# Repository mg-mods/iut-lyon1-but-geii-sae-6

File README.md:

# SAE 6 - Système d'alarme
Repo du projet **SAE 6 "système d'alarme"** réalisé dans le cadre de notre troisième année de BUT GEII à l'IUT Lyon 1.

## Concept initial
Notre projet consiste à développer un système d’alarme domestique complet, prêt à être installé sur une maison.

Les systèmes de surveillance actifs sont des détecteurs d’ouverture de portes et fenêtres ainsi qu’une caméra équipée de reconnaissance faciale à l’entrée.

L’interface utilisateur sera supportée par un M5Stack qui communiquera sans fil, en HF, avec le module central. À ce dernier sont reliés tous les différents composants (capteurs, reconnaissance faciale et alarme). L’interface permettra de verrouiller et déverrouiller le système d’alarme à l’aide d’un code à composer sur l’interface ou d’un badge RFID (à condition que la personne utilisant le badge soit reconnue par la reconnaissance faciale). Lorsqu’une intrusion est détectée, un module d’alarme est déclenché. 

Le module d'alimentation permet, en cas de coupure de courant, d'utiliser l'énergie stockée dans une batterie et de recharger cette dernière une fois le courant rétabli. Ce module d'alimentation est aussi responsable du déclenchement du mode dégradé permettant d'utiliser les modules critiques uniquement afin de réduire la consommation d'énergie. 

La communication étant critique, le système bascule en liaison BLE en cas de problème de communication en HF pour assurer une communication en permanence.

## Cahier des charges
### Cahier des charges initial :
- Détection d'ouverture d'une porte ou fenêtre
- Digicode pour déverrouiller l'alarme
- Reconnaissance faciale
- Alarme sonore
- Communication entre le digicode et la centrale en HF
- Protocole d'appairage entre le digicode et la centrale
- Détection d'erreur ou de signal anormal (sur les liaisons filaires)

### Améliorations possibles :
- Utilisation de badges RFID plutôt qu'un code, mais voir comment rendre cette solution sécurisée
- Communications en BLE si HF non fonctionnel
- Ajout d'une batterie et d'un mode dégradé en cas de coupure de courant
- Détecteur de mouvements
- Ajout d'un module GSM pour appeler le propriétaire et les forces de l'ordre ou un service de sécurité privée
- Ajout d'un bouton panique
- Empreinte biométrique

### Contraintes :
- Nécessité d'utiliser des capteurs à l'état haut par défaut pour détecter les failles
- Différenciation entre un capteur actif et un capteur absent ou endommagé

## Synoptique global initial
Au démarrage du projet, nous avions imaginé un fonctionnement bien précis pour notre système. Nous avons listé toutes les fonctionnalités que nous souhaitions implémenter et les avons reliées ensemble logiquement. L'ensemble du système tel que nous l'avions imaginé, sa décomposition en sous-systèmes et les interactions de ces derniers sont décrits ci-dessous :
[![](https://mermaid.ink/img/pako:eNqVVl1vokAU_SuTeWqz4opKUVKbtmhb0_oR6ma7G15GGJUUGDKMq67xv-8MCgysJa2JD3DuuWfu5dwLe-gQF0MDLnyycVaIMvBi2aEdAv5DPqLB7R7EKxRhAzgedXxcAz6aY98ANrwTOBgRd-1jcDEdmpc2BIcj1wncCqZJggCFbsYdaRI1QF6Yc925rwi-xB7xgPNUiuKoQtbi8BxTugNTLydFG5pz5sRnEmNKNpiCMWYbQt-PFKk3Shy9S1zX-6NQ7Mj81wijd0zjXO1IpNuctsJb-Yxv4CJp7KUsx9uprCWO74VlqR_DQvcVtv1YZPb2XeicHkPxsSlzxKSasI92EvMeMYbprsigC8-tPJv1MOyfnliRGYn-fqx2bL9MzC3ydW7G_FqFCeUT3RS2LNlYCVw_WAaSWkSJE8teTs4XgxEK0RIHOGQ2zMoUdlYcFFT21kQBpkjuDt4yxSWEqjkvJMxZlZl9HgPU_MQpr_kZXjNVlJ8JYNvG_Pa61xuOHybgGzCfBuZzr3eTVFLqpohFIvbpgUfevwxEXGrcM7FOOTadpPQAfI7FnydV6nXlRjJJEZ-f8IRfhJwTlFnzCJdNJ2JVITOd_BxYqdbZKCFmTsb94Ww4Gd-9gIxR6gi3JOD1JTDg7TWf7qzHpMxyGaXhSVQc-SwcKgzzB3mlGqXNBHq9vLdivRW3Fodn1vDxcWBlUcUVJcSeB79eZ9bkefB60ikuJXDGH4UgsU64kDnpDzJM8tj18YiZOf4fN5BHlEfpBB27XxoXIPnmlKk0GGcj0jyZlbgD9wCFXoCYR0IDLFDMpJcNN2Al7FTCanVytTq5WpE8mccU5bPP6BpL2LwCc85hsAaX1HOhIW7UIN9SvG_8Eu4Fz4ZsxfedDcVGcZF4u9rhgXMiFP4mJEhplKyXK2gskB_zq3Xkco2-h5YUBdldikMXU5OsQwYNVe90m0kaaOzhFhqK1mzU23q7q2taR-u2dK0Gd9Bo6lf1TrvV0lpNXW132u1DDf5NhNW6pnU77YbeVFW1oXWv9BrErscIHR0_lpJvpsM_bDXspg?type=png)](https://mermaid.live/edit#pako:eNqVVl1vokAU_SuTeWqz4opKUVKbtmhb0_oR6ma7G15GGJUUGDKMq67xv-8MCgysJa2JD3DuuWfu5dwLe-gQF0MDLnyycVaIMvBi2aEdAv5DPqLB7R7EKxRhAzgedXxcAz6aY98ANrwTOBgRd-1jcDEdmpc2BIcj1wncCqZJggCFbsYdaRI1QF6Yc925rwi-xB7xgPNUiuKoQtbi8BxTugNTLydFG5pz5sRnEmNKNpiCMWYbQt-PFKk3Shy9S1zX-6NQ7Mj81wijd0zjXO1IpNuctsJb-Yxv4CJp7KUsx9uprCWO74VlqR_DQvcVtv1YZPb2XeicHkPxsSlzxKSasI92EvMeMYbprsigC8-tPJv1MOyfnliRGYn-fqx2bL9MzC3ydW7G_FqFCeUT3RS2LNlYCVw_WAaSWkSJE8teTs4XgxEK0RIHOGQ2zMoUdlYcFFT21kQBpkjuDt4yxSWEqjkvJMxZlZl9HgPU_MQpr_kZXjNVlJ8JYNvG_Pa61xuOHybgGzCfBuZzr3eTVFLqpohFIvbpgUfevwxEXGrcM7FOOTadpPQAfI7FnydV6nXlRjJJEZ-f8IRfhJwTlFnzCJdNJ2JVITOd_BxYqdbZKCFmTsb94Ww4Gd-9gIxR6gi3JOD1JTDg7TWf7qzHpMxyGaXhSVQc-SwcKgzzB3mlGqXNBHq9vLdivRW3Fodn1vDxcWBlUcUVJcSeB79eZ9bkefB60ikuJXDGH4UgsU64kDnpDzJM8tj18YiZOf4fN5BHlEfpBB27XxoXIPnmlKk0GGcj0jyZlbgD9wCFXoCYR0IDLFDMpJcNN2Al7FTCanVytTq5WpE8mccU5bPP6BpL2LwCc85hsAaX1HOhIW7UIN9SvG_8Eu4Fz4ZsxfedDcVGcZF4u9rhgXMiFP4mJEhplKyXK2gskB_zq3Xkco2-h5YUBdldikMXU5OsQwYNVe90m0kaaOzhFhqK1mzU23q7q2taR-u2dK0Gd9Bo6lf1TrvV0lpNXW132u1DDf5NhNW6pnU77YbeVFW1oXWv9BrErscIHR0_lpJvpsM_bDXspg)

## Synoptique global final
À la fin du projet, certaines fonctionnalités n'ont pas pu être réalisées, que ce soit pour des raisons budgétaires ou que ces parties étaient trop chronophages. L'ensemble du système final, sa décomposition en sous-systèmes et les interactions de ces derniers sont décrits ci-dessous :
[![](https://mermaid.ink/img/pako:eNqNlV1v2jAUhv-K5atOI4x8AG1Upk6BtohRUGBaN-XGSQxETezIMYMO8d9nB0iclNEicZG87-NzfM6xs4MBDTG04SKmm2CFGAffXY94BIgfihFL7nYgW6EU2yCIWBDjBoiRj2MbePCb1MGYhusYg6vp0PnkQbA_sEESXiAdmiSIhAU7bitogiJSsqEfa5JX6LEwnEcZytILYV0h-5ixVzCNSijdsJLxacwVYko3mIEnzDeUvRwQpTZalr4obBwRjeFA5WcpRi-YZSoqSqOtt8oOoz917MewUkmNb5kCrPBW8c6fv7jP4OpY0moLNLaIwosJuvfD_rGWao6yBx-JKltRa52WhHGyTHhJpowGmdq_PFwGxoigJU4w4R4sIssWagFKLmbtoAQzpCaMt1wLKWV6yRHKg1Wd7AsP0MuMT5zxEc54y5nvcGPKMJDG7LhHtcKAb1v-3W2vN3y6n4DPwHkcOKNe72tehFojpBdJ7-O9dJym4owrkK65O3x4GLjSmo_qKawYdvkXYbVmUytEKVUMOhKG6eTnwJUuuX5V9lW5TLdqClSTyLhyeECvV2SXH6Tq-QBiE6PBr9ncnYwGs-OWqycCnKlcxSSnX4RxJv1BoSnVvz1kUBTv7QyD0lGfz6N02HptBsGhtupKtWl712GedZwiFWUWfdwBRKIE8YgSGyxQxpV7TXTxovwOHfxfzqfxpIrh52yNFc2_oAXnNNiASxaF0JYvGlAcb7Fz8Qh3kvMgX4mLwoPySIVIXsUe2QsmReQ3pckJY3S9XEF7geJMPK3TUMToR2jJUGnBJMTMoWvCoa23u_ka0N7BLbStblPvmkbLaOtWx7q2rAZ8laZO02iZht5pt42uaZnX-wb8m0dtNbtWW78xdat1Ywm9YzYgDiNO2fjwWc2_rvt_SVRXbA?type=png)](https://mermaid.live/edit#pako:eNqNlV1v2jAUhv-K5atOI4x8AG1Upk6BtohRUGBaN-XGSQxETezIMYMO8d9nB0iclNEicZG87-NzfM6xs4MBDTG04SKmm2CFGAffXY94BIgfihFL7nYgW6EU2yCIWBDjBoiRj2MbePCb1MGYhusYg6vp0PnkQbA_sEESXiAdmiSIhAU7bitogiJSsqEfa5JX6LEwnEcZytILYV0h-5ixVzCNSijdsJLxacwVYko3mIEnzDeUvRwQpTZalr4obBwRjeFA5WcpRi-YZSoqSqOtt8oOoz917MewUkmNb5kCrPBW8c6fv7jP4OpY0moLNLaIwosJuvfD_rGWao6yBx-JKltRa52WhHGyTHhJpowGmdq_PFwGxoigJU4w4R4sIssWagFKLmbtoAQzpCaMt1wLKWV6yRHKg1Wd7AsP0MuMT5zxEc54y5nvcGPKMJDG7LhHtcKAb1v-3W2vN3y6n4DPwHkcOKNe72tehFojpBdJ7-O9dJym4owrkK65O3x4GLjSmo_qKawYdvkXYbVmUytEKVUMOhKG6eTnwJUuuX5V9lW5TLdqClSTyLhyeECvV2SXH6Tq-QBiE6PBr9ncnYwGs-OWqycCnKlcxSSnX4RxJv1BoSnVvz1kUBTv7QyD0lGfz6N02HptBsGhtupKtWl712GedZwiFWUWfdwBRKIE8YgSGyxQxpV7TXTxovwOHfxfzqfxpIrh52yNFc2_oAXnNNiASxaF0JYvGlAcb7Fz8Qh3kvMgX4mLwoPySIVIXsUe2QsmReQ3pckJY3S9XEF7geJMPK3TUMToR2jJUGnBJMTMoWvCoa23u_ka0N7BLbStblPvmkbLaOtWx7q2rAZ8laZO02iZht5pt42uaZnX-wb8m0dtNbtWW78xdat1Ywm9YzYgDiNO2fjwWc2_rvt_SVRXbA)

## Organisation du repo
Chaque composant sera réparti dans des branches différentes de ce repo. Voici la liste des branches présentes :
- **main** : branche d'accueil du repo, laissée vide pour l'instant
- **alarm** : branche du module d'alarme (réalisée par Lilian CHARRIERE)
- **cmd** : branche du module de commande (ou "digicode", bien que cette appellation soit assez réductrice ; réalisée par Corentin DEBAISIEUX)
- **hf** : branche des transmissions HF et de la modulation du signal (réalisée par Gaspard DENIZOU)
- **hub** : branche du module principal (ou "hub" ; réalisée par Bastien PORTIER)
- **rasp** : branche du module de reconnaissance faciale (réalisée par Lilian CHARRIERE)

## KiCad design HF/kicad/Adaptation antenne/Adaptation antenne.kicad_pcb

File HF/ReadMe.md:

# Modulation haute fréquence

## Diagramme de fonctionnement théorique

| | Valeur |
| ------ | ------ |
| Signal UART | 9600 bps |
| Fréquence porteuse | 100 kHz |
| Fréquence d'émission | 13,56 MHz |
| Puissance d'émission | 10 dBm |

```mermaid
---
config:
  theme: forest
  themeVariables:
    lineColor: '#FFA100'

---

stateDiagram
  direction TB
  state modulation {
    direction TB
    Mi1 --> V1
    Ol1 --> PB1
    V1 --> PB2
    PB2 --> Me1 :Tension=100mVpp P = 14DBm
    PB1 --> Me1 :Tension =1 a 2 Vpp P = 4-10DBm
    Me1 --> [*]
    Mi1
    V1
    Ol1
    PB1
    PB2
    Me1
  }
  state Démodulation {
    direction TB
    [*] --> G
    G-->PD
    PD --> Me2
    Ol2 --> Me2
    Me2 --> PB3
    PB3 --> PLL
    PLL --> PB4
    PB4 -->trig
     trig -->Mi2
[*]    Me2
    Ol2
    PB3
    PLL
    Mi2
  }
  modulation --> Démodulation
  Mi1:Microcontrôleur
  V1:VCO
  Ol1:Oscillateur local 13 MHz
  PB1:Filtre passe-bas fc=13,56 MHz
  PB2:Filtre passe-bas Fc=100 kHz ordre 2
  Me1:Mélangeur
  Me2:Mélangeur
  Ol2:Oscillateur local 13 MHz
  PB3:Filtre passe-bande centré sur 100 kHz ordre 2
  PB4:Filtre passe-bas Fc=20 kHz ordre 2
  trig:Trigger de Schmitt
  PD:Pont de diodes
  G:Gain 10 dBm
```

Le gain de la partie démodulation se fait avec un AOP transimpédance si, à la sortie de l'antenne, on doit amplifier le signal.  
Le pont diviseur sert à bien avoir la bonne puissance en entrée du mélangeur.

## Simulation LTspice

Le VCO, la PLL et les mélangeurs n'étant pas répertoriés sur LTspice, ils sont simulés avec des lignes de commande.

| Composant | Ligne de commande |
| ------ | ------ |
| VCO modulation | `Bvco vcomod 0 V = 2.5 + 2.5*sgn(sin(2*pi*idt( {Fp}*(1 + 0.05*(V(microout) - 0.5)) )))` |
| Mélangeur modulation | `bvmel1 mel 0 V = V(filtre_100k)*V(filtre_13M)` |
| VCO démodulation | `Bvcodemod Vco 0 V = 2.5 + 2.5*sgn(sin(2*pi*idt( {Fp}*(1 + 0.1*(V(Demodul) - 0.5)))))` |
| Mélangeur démodulation | `bvmel2 mel2 0 V = V(mel)*V(oscilateur)` |

### Paramètres de simulation

| Paramètre | Valeur |
| ------ | ------ |
| Tsim | 5 ms |
| F | 9600 Hz |
| F13 | 13 560 000 Hz |
| Fp | 100 000 Hz |

## Schémas KiCad théoriques

L'adaptation d'impédance de l'antenne se fait sur une petite carte reliée par un câble BNC.

## Mise en pratique

Lors de la livraison des composants, nous n'avons pas reçu de 74HC4046 mais des CD4046BE. Bien que ce composant ait les mêmes fonctionnalités que le composant que nous avions choisi, son dimensionnement est bien différent pour les valeurs de résistance nécessaires.

Le VCO n'oscille plus à 100 kHz mais autour de 130 kHz. C'est entre autres dû à la datasheet du composant, qui n'est pas très lisible :

[lien datasheet CD4046BE](https://www.ti.com/lit/ds/symlink/cd4046b.pdf?HQS=dis-dk-null-digikeymode-dsf-pf-null-wwe&ts=1780683578275&ref_url=https%253A%252F%252Fwww.ti.com%252Fgeneral%252Fdocs%252Fsuppproductinfo.tsp%253FdistId%253D10%2526gotoUrl%253Dhttps%253A%252F%252Fwww.ti.com%252Flit%252Fgpn%252Fcd4046b)

## Travail réalisé

- [x] VCO et modulation à basse fréquence
- [x] PLL et démodulation à basse fréquence
- [ ] Utilisation du mélangeur pour basculer en haute fréquence
- [ ] Adaptation en impédance de l'antenne
- [ ] Utilisation du mélangeur pour basculer en basse fréquence

## Test de bon fonctionnement

Pour vérifier le bon fonctionnement, j'ai effectué des mesures à l'oscilloscope en entrée et en sortie d'une liaison VCO-PLL avec, en entrée et en sortie, un microcontrôleur RP2040 choisi pour ses deux canaux UART et parce que les tensions de sortie UART correspondent aux microcontrôleurs utilisés dans notre système de surveillance (soit 3,3 V).

J'ai ensuite envoyé une série de 100 messages similaires à ceux qui sont envoyés entre le digicode et le hub, puis j'ai comparé le message d'origine avec le message reçu.

J'ai au maximum 10 messages reçus avec une erreur ou plus, soit 10 % d'erreur maximale de transmission en basse fréquence.

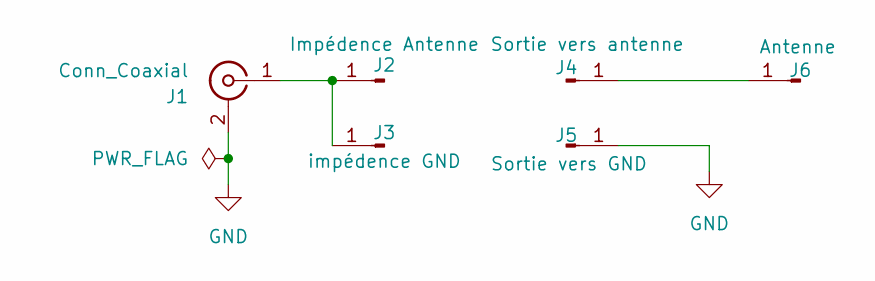
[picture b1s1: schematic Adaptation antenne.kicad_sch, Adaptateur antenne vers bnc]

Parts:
J1: Conn_Coaxial; Adaptateur BNC
J2: Impédence Antenne; PinHeader_1x01_P1.00mm_Vertical
J3: impédence GND; PinHeader_1x01_P1.00mm_Vertical
J4: Sortie vers antenne; PinHeader_1x01_P1.00mm_Vertical
J5: Sortie vers GND; PinHeader_1x01_P1.00mm_Vertical
J6: Antenne; PinHeader_1x01_P1.00mm_Vertical

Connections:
GND: J1.2 (Ext), J5.1
unnamed: J1.1 (In), J2.1, J3.1
unnamed: J4.1, J6.1

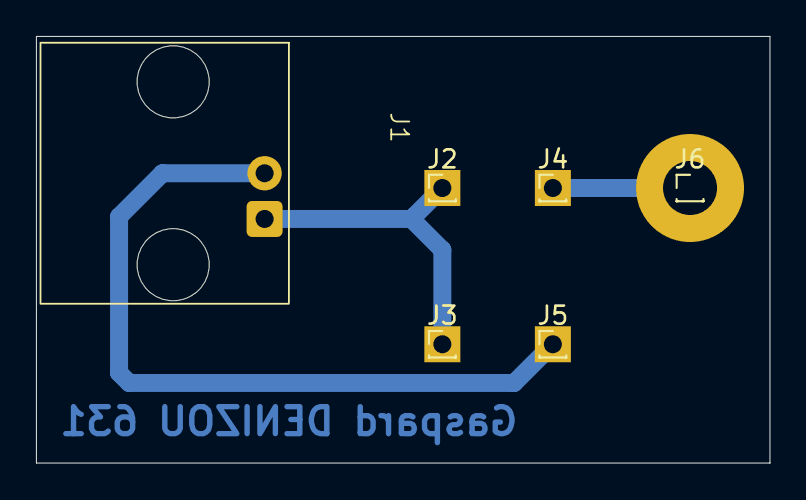
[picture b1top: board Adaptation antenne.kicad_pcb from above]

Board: 2 copper layers, 40.8 x 23.7 mm, 6 parts (0 on the bottom side), 3 nets.

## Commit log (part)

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2026-01-22 Premier essais
    Push and commit d'essais
2026-01-22 Add initial Hub project files and assets
    Added PlatformIO configuration, source, header, and documentation files for the Hub project targeting the M5Stack Core2 board. Included .gitignore, VSCode extension recommendations, image assets, and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
2026-01-22 ajout simulation du sommateur sur LTspice
2026-01-22 tentative PLL LTspice n°1
2026-01-23 Version bien de l'interface + sous-menu
    Removed houseLock.h and added images.h to manage image resources. Updated main.cpp to use the new images header. Replaced house-lock PNG with new SVG assets (exit, gear, restart, siren) and updated I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
2026-01-23 simu de la modulation et démodulation à 100k de porteuse
2026-01-27 Amélioration globale de l'interface
    Buttons are now managed via pointers with dynamic allocation and cleanup to improve memory handling. UI layout for options screen is updated for better consistency, and button initialization is separ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
2026-01-27 test rfid+image
2026-01-29 test readme avec schémas mermaid
2026-01-29 mermaid 2.0
2026-01-29 mermaid 3.0
2026-01-29 changement theme de mermaid
2026-01-29 changegement couleur ligne du schémas mermaid
2026-01-29 changement position filtre du schémas mermaid
2026-01-29 réparation des pb du schémas
2026-01-29 Connexion serie + affichage sur screen + ébauche RTC
    Introduces FreeRTOS queues and tasks for serial message reception and LCD display management. Adds message parsing, logging with timestamps, and dynamic display of messages on the home screen. Refact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
2026-01-30 Communication série interM5 fonctionnel
    Replace dynamic String with fixed char msg[TRAME_SIZE] in t_message_lcd to avoid heap allocations and copy incoming payloads with snprintf. Switch serial I/O to Serial2 (begin on pins 13/14 at 9600) 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
2026-01-30 Add files via upload
    test pour la liaison serie
2026-02-01 comit fin 2eme semaine
2026-02-07 modif graphique readme , ajout detail filtre et tension
2026-02-07 schemas bloque finit
2026-02-07 choix et dimmentionement presque terminer
2026-02-24 ajout fichier ltspice schémas total
2026-02-24 schémas de simulation de la liaison hf finit
2026-02-24 3-line scrolling display and serial parsing fix
    Introduce a 3-line scrolling buffer for the LCD and simplify serial message parsing. Incoming 'L...' frames no longer use a numeric line index; the code logs the full text, stores it in the message, 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
2026-02-24 Add files via upload
    ajout de task
2026-02-26 Passage du défilement à 4 lignes
    Increase the R1 region height from 80 to 85 for a slightly larger UI element. Remove an unused assignment to message.ligne. Expand the displayBuffer from 3 to 4 lines, adjust the scrolling copies and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
2026-02-26 Amélioration du défilement + post-factorisation
    Introduce a global displayBuffer[4][64] to hold the four LCD lines and initialize it in setup. drawHome now renders these buffered lines, and taskGestionLcd was updated to use the global buffer (loca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
2026-02-26 Factorisation du code
2026-02-27 Détection trame via Regex + check keyboard password OK
    Introduce regex-based parsing and password verification: add <regex> include and KEYBOARD_PWD constant, implement comparePwd() to respond TRUE/FALSE on Serial2, and call it when receiving VerifPWD fr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
2026-03-03 debut test task+ synch
    ajout de mainbak; programme v1 ok sans task
    main contient un test avec les task, contient qlq erreur
2026-03-03 Réception/émission demande longueur MDP
    Update main.cpp to better handle MDP length requests and unify logging:
    - Add forward declaration for taskGestionLcd.
    - Change regex for length request from "ASKLenght/0000" to "AskLenghtMDP/0" and update comment.
    - Respond to length requests by computing KEYBOARD_PWD length, sending a formatted "str/.../LenghtMDP/..." message, and logging the value.
    - Replace some Serial.println calls with logSerial and switch SysSerial.printf to Serial.printf in logSerial for consistent output.
    These changes ensure correct detection and response to password-length queries and centralize serial logging.
2026-03-03 Comm mdp filaire avec clavier 100% fonctionnelle
    Introduce RFID_PWD constant and enable Serial2 usage. Change comparePwd to return a String and update taskTraiteTrame to match new protocol strings ("str/..." and "MDPInput/LenghtMDP/StatePass"). Sen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
2026-03-03 Mise en place du RFID fonctionnel
2026-03-03 Mise en fonction pour factorisation du code
2026-03-03 filtre en ordre 2+ passage en alternatif+ ajout sur kicad + ajout kicad interrupteur pour piloter l'entré/ sortie de l'antenne. manque plus que le gain en sortie du mélangeure
2026-03-06 Ajout0 MUTEX pour désactivation alarme via clavier
    Introduce a mutex (lcdMutex) to protect concurrent access to the M5.Lcd and wrap LCD drawing in xSemaphoreTake/xSemaphoreGive. Refactor and consolidate UI logic: add screen management and drawing fun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
2026-03-06 Résolution d'un bug d'affichage sur le menu Options
    Modify taskGestionLcd to only process queueAffichage messages when currentScreen == HOME, preventing LCD updates from occurring while other screens are active. Also includes an updated binary Rapport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
2026-03-06 Ajout taskTraiteInput et ajustement mineurs
    Comment out an extra logSerial call in handleAskStateAlarm and emit StateAlarm on both Serial2 and Serial for visibility. In handleMDPInput rename the verification variable to stringPWD, emit StateMD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
2026-03-26 modif readme
2026-03-26 Ajout lecture d'un GPIO
    Add a stub task taskTraiteSensor and create it pinned to core (placeholder for sensor processing). Register pin 19 as INPUT in setup and remove the temporary digitalRead test in loop (commented out).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
2026-03-26 Add motion_detector image array
    Add a new PROGMEM image resource motion_detector to Code/hub/Hub/src/images.h as a const unsigned short array. The array is currently populated with zeros (placeholder/empty bitmap). main.cpp was als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
2026-03-26 Affichage correct image détection mouvement
    Reduce the large static motion_detector bitmap data in images.h (removed/replaced long sequence of 0x0000 entries) and update main.cpp to match the revised image resource. This change simplifies the 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
2026-03-26 ajout carte adaptation pr antenne + comparateur pour sortie demodulation
2026-03-26 modif schémas de simulation
2026-03-26 Add ALARM screen and sensor/MDP handling
    Introduce an ALARM screen (enum + draw/init functions) and wire it into setScreen. Consolidate and relocate handleMDPInput, send password verification over Serial2 and toggle lock on success. Revise 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
2026-03-26 main.cpp fix i2c
    les taches ne se coupe plus pendant les émission reception i2c. les 3 task sont opérationnel. otimisation par fonction a prévoir
2026-03-27 Ajout de l'activation de la sirène
2026-03-27 Ajout de la reco faciale pour le RFID
2026-03-27 modif kicad pour ajusté au test sur platin
2026-04-02 Ajout alarme LED + un peu avancé le rapport
    Add FastLED dependency and control the M5GO Bottom2 LED bar. platformio.ini: add fastled/FastLED@3.6.0. main.cpp: include <FastLED.h>, define LED_PIN/NUM_LEDS and CRGB leds[], initialize LEDs in setu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
    Implement visual alarm behavior: use orange ambient color when armed, clear LEDs when alarm is off, light LEDs orange when armed, and blink LEDs red during ALARM via new BlinkLeds(). Update button la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
    Persist state across restarts: rename preference
2026-04-02 Non-blocking alarm LED blink and MAC handling
    Refactor main.cpp to make alarm LED blinking non-blocking and improve ID/MAC handling.
    - Replace blocking BlinkLeds implementation (delay/while) with millis-based toggle and brightness changes to avoid blocking tasks.
    - Call BlinkLeds from loop() when on ALARM screen; remove direct blocking call from drawAlarm().
    - Add getMacFactory() to read device MAC (ESP32) as a String.
    - Broaden regex patterns in taskTraiteTrame to accept MAC-like ID strings and colons; replace placeholder ID constants with sample MAC/ID values.
    - Adjust LED behavior on locked/home states: use CRGB::OrangeRed and set brightness; set brightness in BlinkLeds toggles.
2026-04-03 Factorisation, changement couleurs, LED, appairage + comm appairage OK
    Add hub/device ID state and pairing support; introduce handlePairing, checkMACisInROM and fadeLeds. Update message parsing with stricter regexes, centralize routing in taskTraiteTrame, and add serial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
2026-04-03 apparing add, saving mac hub ok.+ architectur rebuild
2026-05-07 apparing ok+ menu ok
2026-05-07 Appairrage fonctionnel avec menu dédié
    Introduce a PAIRING screen and pairing mode to handle device appairage. Adds isPairingMode flag, new UI functions (initPairingButtons, drawPairing, handlePairingLogic), and wiring to setScreen/loop t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
2026-05-07 Correction d'un bug RFID
    Relax the RFID input regex to accept 12–17 character identifiers instead of requiring exactly 17 characters. Comment out the call that resets the stored MAC on startup to avoid unintentional clears (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
2026-05-07 mdp a validé+bt del+ upgrade menu
2026-05-07 Add change-PIN and RFID badge list UI
    Introduce dynamic keyboard PIN and RFID badge management: replace static KEYBOARD_PWD with keyboardPwd (stored in Preferences) and add rfidBadges (std::vector<String>) with persistent load/save (rfid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
2026-05-07 modification readme
2026-05-07 modification pour incorporer une image
2026-05-07 modif lien
2026-05-07 Add RFID/pwd handling and UI/serial refactor
    Large refactor and feature additions for Hub main.cpp: reorganized constants, globals and comments; added mutex protection for LCD and clarified pin/LED setup. Implemented serial command handling enh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
2026-05-21 Add LCD notifications, extend RFID regex, fix logic
    Send LCD queue messages for RFID badge, keyboard password change, and RFID add events; extend RFID/Add/Del regex length limits from 17 to 25 chars to accept longer tags. Add logSerial(buffer) to trac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
2026-05-21 password admin ok
2026-05-21 Add admin password support and UI changes
    Introduce a separate admin PIN (PassAdmin) with storage in preferences and remote verification. Adds compareAdminPwd(), handlePassAdminInput(), and a regex to recognize PassAdminInput frames; the ser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
2026-05-21 ajout time histo
    surement une des derniere version
2026-05-21 commentaire Doxygen
2026-05-21 Fix password color logic; add IHM docs
    Corrected color assignment for password UI: index 9 now uses C_GREY instead of C_RED in drawChangePwd and handleChangePwdLogic, keeping the visual state consistent with isAdminPwdChange. Also added a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
2026-05-22 logic rfid reparé
2026-05-22 ajustage de commentaire
2026-05-23 Rédaction des différentes docs
    Tweak Compte-rendu attendu.md (adjusted strikethrough content in the INFO section) and update several binary documentation files (Dossier conception.docx, IHM_Hub.odg, Rapport communication.docx). Re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
2026-05-24 Amélioration mineur du code, avancement des documents et des commentaires
2026-06-05 ajout de la documentation digicode
2026-06-06 ajout photo et modification readme
2026-06-06 correction liens des images
2026-06-06 mise a jours schemas kicad
2026-06-07 readme corigé
2026-06-07 ajout readme projet
2026-06-07 Ajout du dossier de conception en .pdf
2026-06-07 Réorganisation fichiers
2026-06-08 Updated ReadMe, added files
2026-06-08 Added facial_recognition project folder
2026-06-10 Added text that was apprently missing... I remember writing it but ok
2026-06-10 Fixed incorrect text alignment
